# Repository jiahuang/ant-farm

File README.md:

ant-farm
========

Fuse the bits to clock the Attiny at 8mHz

lfuse sets the 1mHz internal clock
hfuse sets brownout detector at 2.0v

```
avrdude -p attiny24 -P /dev/cu.usbmodemfd121 -c avrisp -b 19200 -U lfuse:w:0x62:m -U hfuse:w:0xd8:m -U efuse:w:0xff:m
```

check the port that the attiny is connected to ```ls -l /dev/cu.*```

Increment the UUID and stick on the code
```
python build.py; make all; avrdude -p attiny24 -P /dev/cu.usbmodemfd121 -c avrisp -b 19200 -U flash:w:ant.hex;
```

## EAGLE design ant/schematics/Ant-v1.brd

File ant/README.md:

#Ant

##PCB Schematic

##Wiring diagram

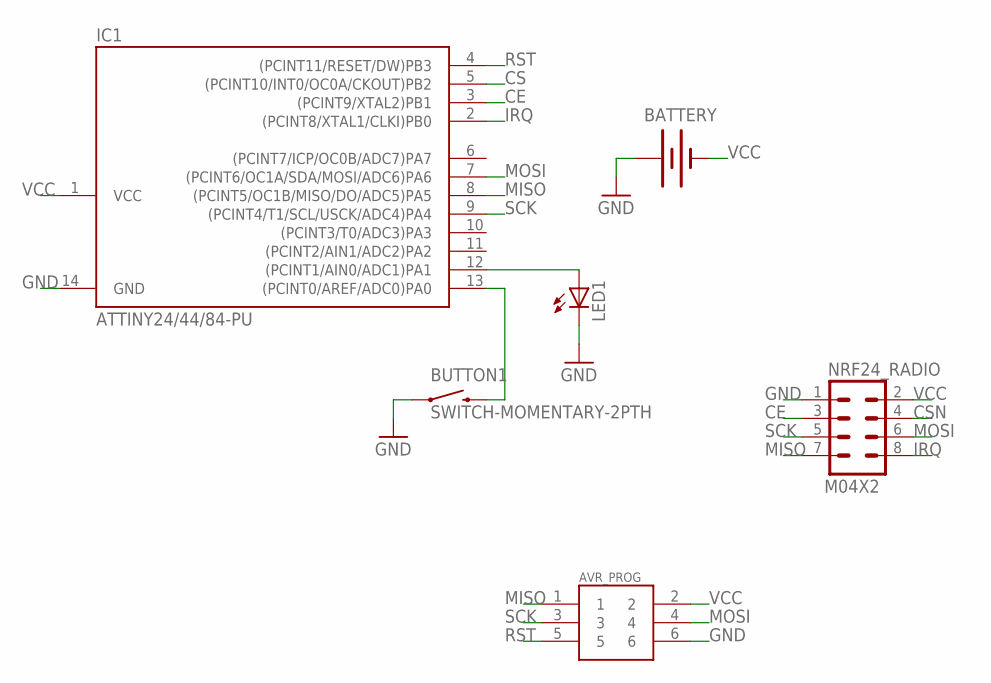
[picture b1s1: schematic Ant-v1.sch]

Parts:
AVR_PROG: M03X2; 2X3-SHROUDED
BATTERY: BATTERY20PTH; BATTCOM_20MM_PTH
BUTTON1: SWITCH-MOMENTARY-2PTH; TACTILE-PTH
IC1: ATTINY24/44/84-PU; DIL14
LED1: LED3MM
NRF24_RADIO: M04X2; 2X4

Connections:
CE: IC1.3 ((PCINT9/XTAL2)PB1), NRF24_RADIO.3
CS: IC1.5 ((PCINT10/INT0/OC0A/CKOUT)PB2)
CSN: NRF24_RADIO.4
GND: AVR_PROG.6, BATTERY.1 (+), BUTTON1.1, IC1.14 (GND), LED1.K (C), NRF24_RADIO.1
IRQ: IC1.2 ((PCINT8/XTAL1/CLKI)PB0), NRF24_RADIO.8
MISO: AVR_PROG.1, IC1.8 ((PCINT5/OC1B/MISO/DO/ADC5)PA5), NRF24_RADIO.7
MOSI: AVR_PROG.4, IC1.7 ((PCINT6/OC1A/SDA/MOSI/ADC6)PA6), NRF24_RADIO.6
unnamed: IC1.12 ((PCINT1/AIN0/ADC1)PA1), LED1.A
unnamed: BUTTON1.3 (2), IC1.13 ((PCINT0/AREF/ADC0)PA0)
RST: AVR_PROG.5, IC1.4 ((PCINT11/RESET/DW)PB3)
SCK: AVR_PROG.3, IC1.9 ((PCINT4/T1/SCL/USCK/ADC4)PA4), NRF24_RADIO.5
VCC: AVR_PROG.2, BATTERY.2 (-), IC1.1 (VCC), NRF24_RADIO.2

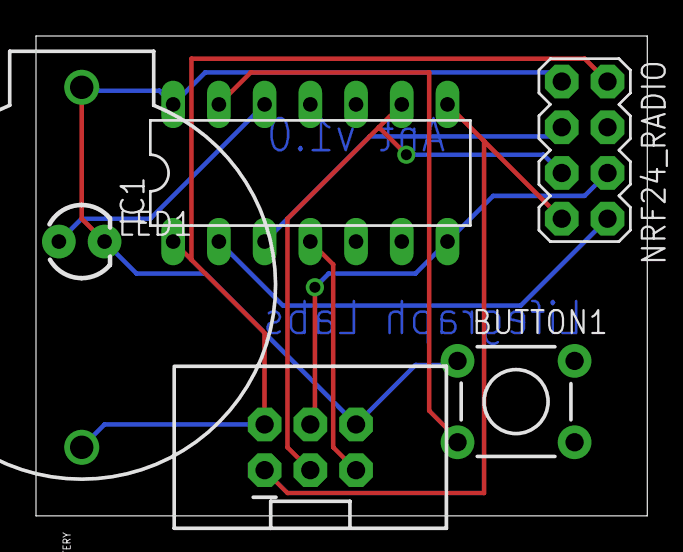
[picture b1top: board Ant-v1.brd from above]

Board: 2 copper layers, 34.0 x 26.7 mm, 6 parts (0 on the bottom side), 10 nets.

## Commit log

2012-11-23 adding readmes
2012-11-23 added ant schematics
2012-11-23 updating readme
2012-11-23 fixing readme
2012-11-23 adding auth token for image
2012-11-23 added auth token for wiring diagram
2012-11-24 basic ant setup
2012-11-24 ignoring makefiles
2012-11-24 adding solider
2012-11-27 i cant spell :c
2012-11-28 message passing between ant and soldier
2012-11-28 Started adding uuid code
2012-11-28 adding files
2012-11-28 updaing with command
2012-11-29 got button flash working
2012-11-29 adding UUID generation
2012-11-29 fixed build output
2012-11-29 wrapping around if id gets too big
2012-11-30 cleaning up nordic code
2012-11-30 bumped max id down to FFFFFF
2012-11-30 reducing power consumption on the ant
2012-11-30 adding instructions for clocking
2012-11-30 fixed padding to 4 bytes
2012-11-30 Added EEPROM functions
2012-11-30 Completed the UUID package
2012-12-02 Added queen iso
2012-12-03 fuse for brownout detection
2012-12-03 splitting into tx
2012-12-03 adding receiving code
2012-12-03 ant code is now receiving
2012-12-03 bumped receiving byte size up to 8
2012-12-03 ant now sends and receives
2012-12-03 ant sending 8 bytes and queen reading those 8 bytes
2012-12-03 queen code reads values from ant
2012-12-04 adding hardware_server.js
2012-12-04 appending queen uuid
2012-12-04 Aded random number between range
2012-12-04 added receiver_only to be able to listen on the RF channel
2012-12-04 Finished Preliminary Ant Code
2012-12-05 Removed unused uuid files
2012-12-06 adding IRQ to the IRQ pin
2012-12-06 adding RX_DR, TX_DS, and MAX_TX pins
2012-12-06 sleep until IRQ trips
2012-12-06 pinging and ponging
2012-12-06 adding another LED. Switched Analog voltage to pin 3
2012-12-06 sleep code works
2012-12-07 bumped up transmit power
2012-12-07 working transceiver code
2012-12-07 receive data reads 8 bytes
2012-12-07 now drops other received ant messages
2012-12-07 Change endpoints for queen_listener
2012-12-07 Switched from Analog Voltage UUID to build scripts :(
2012-12-08 Modified readme to include build script command
2012-12-08 Fixed the sleep code and updated the correct fuses
2012-12-08 BOD Fuse bit set to 2.0V instead of 1.8V to protect the nRF24
2012-12-08 Queen's don't listen for other queen's anymore
2012-12-09 updating readme to 2v BOD
2012-12-09 adding random delay to build.py
2012-12-09 adding random delay and delay after receiver config
2012-12-09 Added watchdog timer to reset
2012-12-09 Fixed watchdog code to run every 8 seconds instead of 2
2012-12-09 switching led blinking to not be during transmission
2012-12-10 Updated from us to ms
2012-12-10 Added more flushing code and set the tranceiver to receive on reset
2012-12-11 Added a delay to the WD interrupt
2012-12-11 removing unneeded file
2012-12-11 receiving on channel 3 and transmitting on channel 10
2012-12-11 changing build to max out delay at 150ms. this is multipled by 5x in the ant code so we have at least a 5ms delay between different ants
2012-12-11 adding colonies
2012-12-11 upping with colony makefiles
2012-12-11 queen listens on channel 10 only
2012-12-11 cleaning up soldier
2012-12-12 setting a higher floor on the delay
2012-12-13 Added ping ids
2012-12-13 Added post to queen_listener
2012-12-15 Adding sign up page
2012-12-15 Fixed a bug on the sign up page
2012-12-16 updaing queen listener to behave correctly
2012-12-16 list of all ant ids
2012-12-16 adding queen id
2012-12-16 my queen listener pings correctly
2012-12-16 Finished the sign up page. Need to hook up recent adds
2012-12-16 changing to cache 5 payloads at once before sending
2012-12-16 dropped ant_id down to 2 bytes
2012-12-16 dropped max bytes down to 2
2012-12-16 pad ID up to 8 bytes
2012-12-16 queen now listens for 30 byte payloads
2012-12-16 changing listening script for 30 byte payloads
2012-12-16 changing all the default ids
2012-12-17 Polished up Syncing page and finished creating unsync page
2012-12-17 Actually adding the new files for syncing and unsyncing
2012-12-17 adding in payload padding

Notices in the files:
parts and their libraries:
SparkFun-Electromechanical: Licensing: CC v3.0 Share-Alike You are welcome to use this library for commercial purposes.
